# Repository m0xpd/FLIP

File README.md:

# FLIP

This repository describes a 'Bernoulli Gate', intended for switching applications in electronic music.

You can dive straight in to details of the [Eurorack module](https://github.com/m0xpd/Flip/blob/main/Eurorack/README.md), or a [stripboard layout for the circuit](https://github.com/m0xpd/FLIP/tree/main/Stripboard), or read more about the background and operation of this new design, below.

# Background

A Bernoulli Gate, named for Swiss mathematician and physicist [Daniel Bernoulli](https://en.wikipedia.org/wiki/Daniel_Bernoulli), takes a clock or gate input and routes it to one of two outputs, A & B, based on the 
value of an internally generated [Bernoulli Variable](https://web.stanford.edu/class/archive/cs/cs109/cs109.1178/lectureHandouts/070-bernoulli-binomial.pdf). When this (discrete, Boolean) random variable has value 1 the clock is routed to output A, and when the variable has value 0 the clock is routed to output B. The probability of the Bernoulli variable assuming value "1", p, is set by a front panel control (and/or by CV input). The probability of the variable assuming value "0" is (of course) 1-p. 

When the probability is set to p = 0.5, the process is equivalent to a "coin toss"; the input is routed to output A or B based on the outcome of a fair coin toss at each input onset. As p moves from the 0.5 value, the coin becomes increasingly "biased", with the outcome favouring one or other output. Larger values of p favors output A.

Bernoulli Gates have become familiar objects in modular synthesizers, the definitive example being Mutable Instruments' [Branches](https://pichenettes.github.io/mutable-instruments-documentation/modules/branches/) and various clones from other manufacturers. There is also a Bernoulli Gate within Mutable Instruments' [Marbles](https://pichenettes.github.io/mutable-instruments-documentation/modules/marbles/) module (and its clones), which is where it caught my interest. These implementations are achieved in software, running on microcontrollers.

# FLIP - a Hardware Bernoulli Gate

The Bernoulli Gate described in this repository is distinguished by being a completely **hardware realisation**. It generates the Bernoulli variable by a test of the instantaneous value of a linear ramp waveform. This ramp is running at a frequency several orders of magnitude above the clock frequencies typically used in synthesiser timing applications and is asynchronous to such input clocks/gates. Further, the ramp waveform is frequency-modulated by a second asynchronous signal, such that there is no possibility of 'phase' lock between an input clock and a subharmonic of the ramp waveform; the process is sufficiently random.

I should make it clear - I have absolutely nothing against the use of microcontrollers and DSP in modular synths, as I believe my work demonstrates. I designed FLIP for pleasure as a deliberate 'break' from playing with software-based systems in the recent development of my [STRACHEY](https://github.com/m0xpd/STRACHEY) sequencer. I based FLIP in hardware (rather than software) because I wanted the pleasure of something different. 

However, I should also confess to a feeling that we have become too ready to turn to soft solutions. There is something wasteful about having a little microcontroller (like Branches' ATMega88) sitting there doing something as simple as implementing (in that case two) Bernoulli Gates, even though it was *definitively the correct solution* for Mutable's commercial product. But I'm not designing for production - I'm enjoying myself, playing with ideas and materials I find to hand (often literally from the junk box). So - whilst I could easily have implemented my new Bernoulli Gate on an Atmel device or a PIC or similar, I think there remains something interesting and worthwhile in doing it 'old school'. 

I also recognise there are some members of the synth DIY community who actively do not like embedded/DSP. I repeat: **I'm NOT one of them**. But I'm pleased this project will be accessible to them.

Two versions of the hardware for FLIP are described in this repository. First, there is an implementation as a [Eurorack Module](https://github.com/m0xpd/Flip/blob/main/Eurorack/README.md), with full design details of the PCBs and front panel required for the 6HP module seen in the image at the head of this page. Second, I have included a [stripboard layout](https://github.com/m0xpd/Flip/blob/main/Stripboard/README.md) for the circuit for people who wish to build for a different format or who prefer to avoid the expense, delay, and minimum order quantities involved in making PCBs. The schematic for FLIP is presented as a single, system-level circuit in the [stripboard version](https://github.com/m0xpd/Flip/blob/main/Stripboard/README.md), whereas the [Eurorack version](https://github.com/m0xpd/Flip/blob/main/Eurorack/README.md) splits the system into two elements for implementation on two PCBs. Accordingly, those wishing to understand system operation might prefer to look at the schematic in the [stripboard folder](https://github.com/m0xpd/FLIP/tree/main/Stripboard) first. 

FLIP has two controls: the main 'probability' control and a control for the CV attenuverter. Advancing the probability control clockwise increases the probability that output A will be activated. When a positive CV is input, advancing the attenuverter control clockwise also increases the probability that A will 'fire' (the opposite sense applies when a negative CV is input). 

# Demo Video

A [short video](https://youtu.be/AdmhHrzYtKI), introduces FLIP and demonstrates its functions. The video is never going to win any oscars, not least as the camera is out of focus for the central 'demo' section. I don't know what changed between recording the music for the intro and 'closing credits' and the main, central demo portion. However, the message is clear, even if the image is not.    

# License

Material in this repository, including the circuit design and Eurorack implementation of FLIP, is published under a Creative Commons CC BY-SA 4.0 [License](https://github.com/m0xpd/Flip/blob/main/LICENSE.txt)

# Circuit Operation

Operation of the 'FLIP' Bernoulli Gate will now be described in some detail. Reference should be made to [this system-level schematic](https://github.com/m0xpd/Flip/blob/main/Stripboard/Graphics/m0xpd%20FLIP%20Bernoulli%20Gate.jpg) to which the component idents, circuit block names, and node names in the description below refer. [Note that these component idents differ from those used in the Eurorack version.]

FLIP derives a new value of a Bernoulli variable, p (as has been briefly introduced above) at the start of every clock input. This is done by comparing the instantaneous amplitude of a sawtooth wave to a threshold value. 

The sawtooth wave is generated by a 40106 oscillator (the block 'RAMP GENERATOR'), which is tuned (by adjustment of trimmer RV1, which should be set so there is approximately 1V on its wiper) to run at approximately 3.5kHz. The resulting sawtooth runs between voltages defined by the Schmitt trigger points of the 40106's inputs but the sawtooth is shifted to 0V mean by the high pass filter network C1,R3. Comparing this 'Saw' voltage with the fixed threshold voltage, 'Thres' (the magnitude of which is set either by the front panel probability potentiometer RV3 and/or by CV input to J2) produces a new Bernoulli variable, P at the output of the 'THRESHOLD COMPARATOR'. If the threshold is close to the bottom of the sawtooth's voltage range, the probability is close to (logical) one. If the threshold is close to the top of the sawtooth's voltage range, the probability is close to (logical) zero. the threshold voltage has been designed so it can be set slightly above or below the sawtooth's range, locking the probability to 1 or 0 (*and thereby setting the 'A' output on or off, with no switching action*), if required.

The photo below shows the 'Saw' waveform (in Yellow), the threshold voltage, 'Thres', set to just above the bottom of the sawtooth's voltage range (in Magenta) and the resulting Bernoulli variable, 'P' (in Cyan). The FM modulation of the saw oscillator (see below) has been disabled to make the image clearer and the results were captured from the prototype [stripboard](https://github.com/m0xpd/Flip/blob/main/Stripboard/README.md) system.

It is seen that the Bernoulli variable is almost always "1", as expected.

In the practical circuit, frequency response and slew rate limitations in the op-amp used as the comparator constrain behaviour when the threshold is placed closer to the top of the sawtooth's range.

The photo below shows behaviour when the threshold, 'Thres' is at about 50% of the positive range of the sawtooth.

It is seen that the Bernoulli variable is almost always "0"; this is the highest we can take the threshold voltage before it locks the gate "off". Taking the threshold value any higher in the practical circuit causes the comparator to fail to produce any 'non-zero' (in a logical sense) output. This is why the sawtooth wave - and the operation of FLIP - has been limited to 3.5kHz. 

The potential divider at the CV input, J2 (R13,R14) is loaded by the input resistance of the susbsequent attenuverter stage; this "loaded attenuator" produces around 6dB of attenuation in any configuration of the attenuverter. This allows a 5V CV signal to control the system, switching the gate from fully "on" to fully "off", whilst a higher CV input can achieve the same control at a lower attenuverter setting. Obviously, more subtle changes in configuration can be achieved with smaller control voltages, or with lower attenuverter settings.  

The external clock or gate signal is applied via J4 to FLIP's Schmitt trigger input circuit 'CLOCK IN' (with upward switchig threshold of 1.4V and downward threshold of 1.05V) to produce the gate signal, 'Input', which indicates an active input. The start of this input is detected by a typical passive differentiator / diode combination (C10,R30,D8), producing the signal 'dInput'.

The system is built around a trivial state machine which has two states, held on a SR flip-flop. I imlemented the flip-flop on 4001 (NOR) and 4081 (AND) gates, which were to hand (FLIP was designed around 'available materials') and provided sufficient logic resources for the remainder of the system. The transitions for the state machine were sufficient to define the Set and Reset signals:

The flip-flop is 'Set' when there is a leading edge of the clock AND the Bernoulli variable is 1 (Set = P.dInput).

The flip-flop is 'Reset' when 'Input' is false (Reset = _Input).

This system was found to work perfectly well in practical musical application, but offended me, as I understood there was possibility for a 'lock' between  a harmonic of the clock and the sawtooth wave, making the process less than random. I had anticipated this in design and arranged for the sawtooth oscillator to be voltage controlled. A second stage of the 40106 ('FM Osc') is used to implement an oscillator from which a triangular wave (at around 800Hz) is generated. This triangular voltage is used to frequency modulate the sawtooth, effectively removing the possibility of any 'lock' between the sawtooth and a periodic input signal. 

The photo below shows triggering with FM enabled:

In this case, the threshold has been set to approximately 0V and the Bernoulli variable is returning a true value approximately 35% of the time (but not achieving the 50% score of a "fair" system, as the 0V threshold is above the middle of the range determined by the two limiting cases shown in the previous two oscilloscope screen shots). Variation in the period of the sawtooth (and the resulting outputs from the comparator) caused by the frequency modulation is clearly visible.

FLIP's three outputs use a simple 'emitter follower' buffer scheme taught by Ken Stone. The 'A' output follows directly the 'Q' output of the flip-flop. The 'B' output must be derived from additional logic to AND the complemented flip-flop state _Q with the input clock/gate signal. Finally, an output is provided which mirrors the input. This output is driven by a further inversion of _Input, rather than by adding load to the output of the CLOCK IN circuit, which could impact the edge detection circuit.

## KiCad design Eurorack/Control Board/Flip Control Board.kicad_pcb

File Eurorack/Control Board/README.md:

# FLIP Control Board

This folder contains details of the Control Board for the Eurorack implementation of the FLIP Bernoulli Gate.

There is a KiCad [Project file](https://github.com/m0xpd/FLIP/blob/main/Eurorack/Control%20Board/Files/Flip%20Control%20Board.kicad_pro) a [schematic file](https://github.com/m0xpd/FLIP/blob/main/Eurorack/Control%20Board/Files/Flip%20Control%20Board.kicad_sch) and a [PCB file](https://github.com/m0xpd/FLIP/blob/main/Eurorack/Control%20Board/Files/Flip%20Control%20Board.kicad_pcb). 

[JLC](https://jlcpcb.com/) made my prototype PCBs (seen above) and did their usual great job.

There is also a schematic (click on the image below to open a larger version) and a BoM, saved as an [Excel file](https://github.com/m0xpd/FLIP/blob/main/Eurorack/Control%20Board/Files/Flip%20Control%20Board%20BoM.xlsx)

The BoM specifies the PJ398SM ('Thonkiconn') Jacks, Alpha 9mm potentiometer and Song Huei trimmer, which are important for mechanical as well as electrical compatability.

As I've mentioned on the [Main Board page](https://github.com/m0xpd/FLIP/blob/main/Eurorack/Main%20Board/README.md), this is only the second project I've developed in KiCad and I'm still feeling my way around. The only aspect of the control board PCB which I regret is the (default, library) footprint for the transistors Q1:3, which has unnecessarily small and close pads. It works, but it asks a lot during soldering. I will modify this if a "v2" revision is ever made.

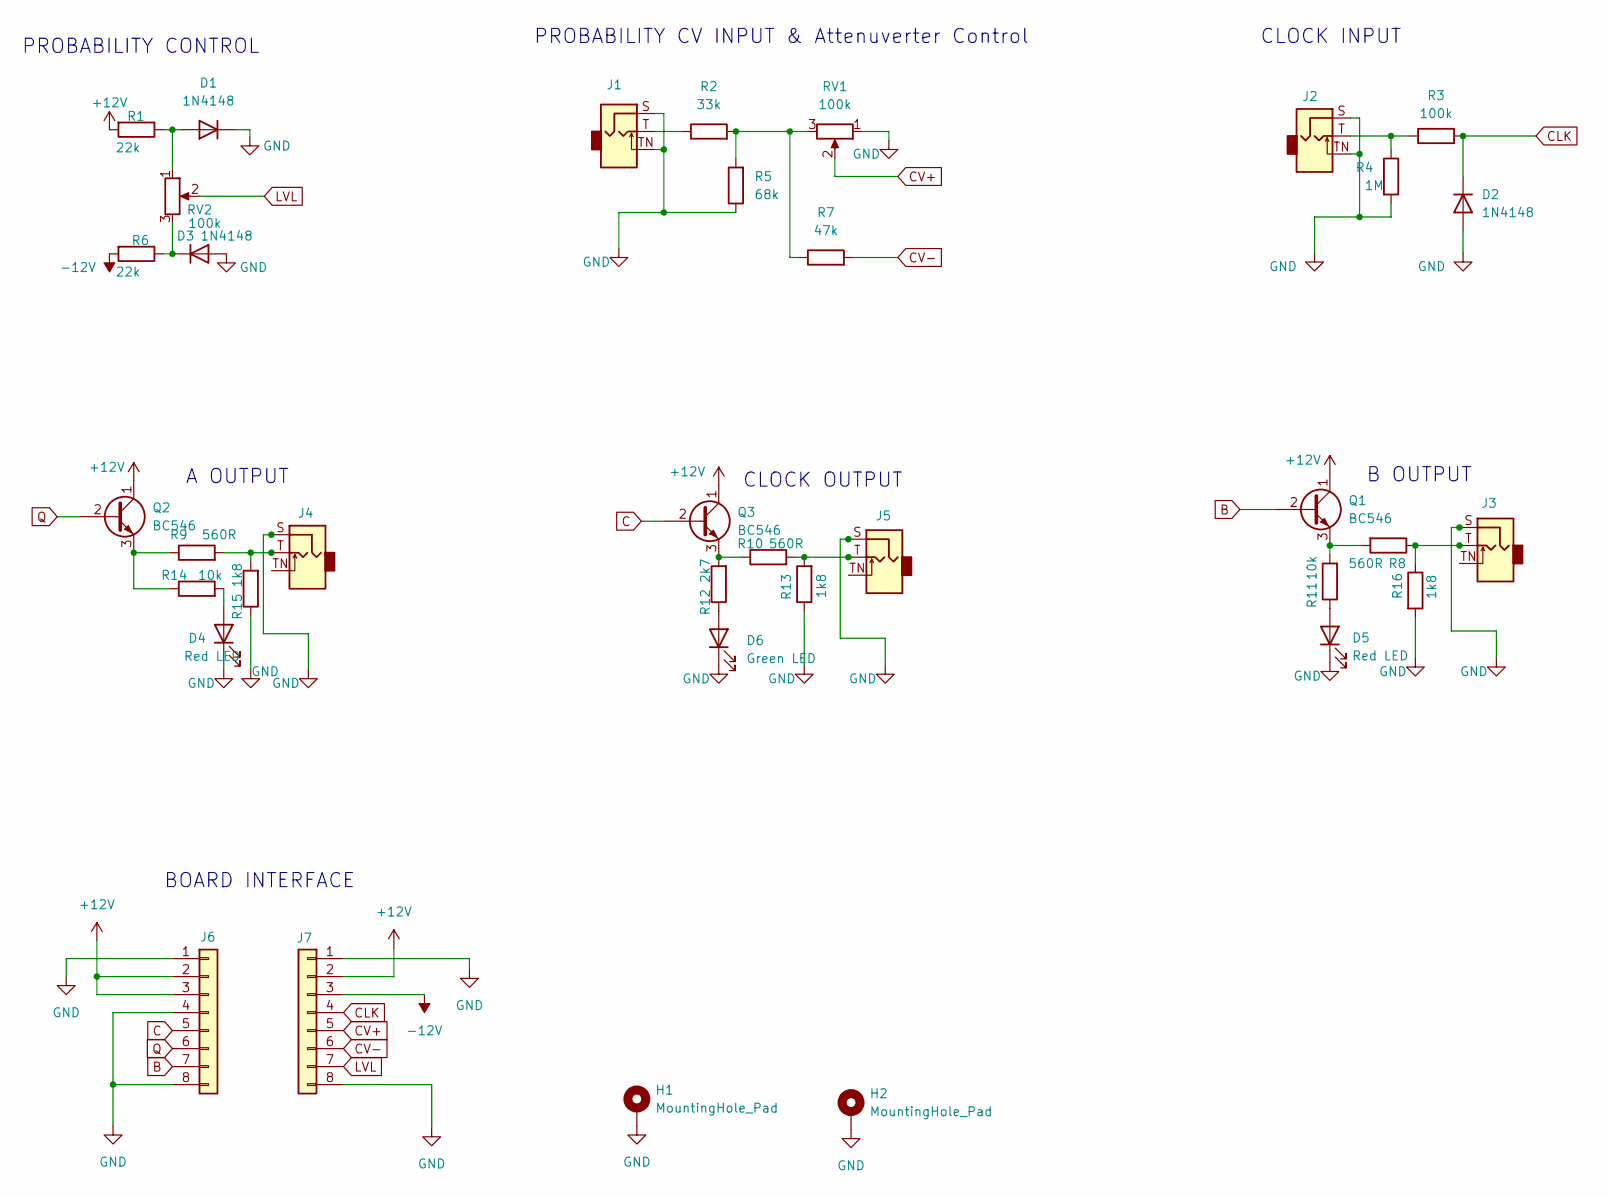
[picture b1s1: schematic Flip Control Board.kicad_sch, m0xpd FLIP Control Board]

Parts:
D1, D2, D3: 1N4148; D_DO-35_SOD27_P7.62mm_Horizontal
D4, D5: Red LED; LED_D3.0mm
D6: Green LED; LED_D3.0mm
H1, H2: MountingHole_Pad; MountingHole_3.2mm_M3_DIN965_Pad_TopBottom
J1, J2, J3, J4, J5: AudioJack2_SwitchT; Jack_3.5mm_QingPu_WQP-PJ398SM_Vertical_CircularHoles
J6, J7: Conn_01x08; PinHeader_1x08_P2.54mm_Vertical
Q1, Q2, Q3: BC546; TO-92_Inline
R1, R6: 22k; R_Axial_DIN0207_L6.3mm_D2.5mm_P7.62mm_Horizontal
R2: 33k; R_Axial_DIN0207_L6.3mm_D2.5mm_P7.62mm_Horizontal
R3: 100k; R_Axial_DIN0207_L6.3mm_D2.5mm_P7.62mm_Horizontal
R4: 1M; R_Axial_DIN0207_L6.3mm_D2.5mm_P7.62mm_Horizontal
R5: 68k; R_Axial_DIN0207_L6.3mm_D2.5mm_P7.62mm_Horizontal
R7: 47k; R_Axial_DIN0207_L6.3mm_D2.5mm_P7.62mm_Horizontal
R8, R9, R10: 560R; R_Axial_DIN0207_L6.3mm_D2.5mm_P7.62mm_Horizontal
R11, R14: 10k; R_Axial_DIN0207_L6.3mm_D2.5mm_P7.62mm_Horizontal
R12: 2k7; R_Axial_DIN0207_L6.3mm_D2.5mm_P7.62mm_Horizontal
R13, R15, R16: 1k8; R_Axial_DIN0207_L6.3mm_D2.5mm_P7.62mm_Horizontal
RV1, RV2: 100k; Potentiometer_Alpha_RD901F-40-00D_Single_Vertical_CircularH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

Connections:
+12V: J6.2, J6.3, J7.2, Q1.1 (C), Q2.1 (C), Q3.1 (C), R1.2
-12V: J7.3, R6.2
B: J6.7, Q1.2 (B)
C: J6.5, Q3.2 (B)
CLK: D2.1 (K), J7.4, R3.2
CV+: J7.5, RV1.2
CV-: J7.6, R7.2
GND: D1.1 (K), D2.2 (A), D3.2 (A), D4.1 (K), D5.1 (K), D6.1 (K), H1.1, H2.1, J1.S, J1.TN, J2.S, J2.TN, J3.S, J4.S, J5.S, J6.1, J6.4, J6.8, J7.1, J7.8, R4.2, R5.1, R13.1, R15.1, R16.2, RV1.1
LVL: J7.7, RV2.2
unnamed: D1.2 (A), R1.1, RV2.1
unnamed: D3.1 (K), R6.1, RV2.3
unnamed: D4.2 (A), R14.2
unnamed: D5.2 (A), R11.1
unnamed: D6.2 (A), R12.1
unnamed: J1.T, R2.1
unnamed: J2.T, R3.1, R4.1
unnamed: J3.T, R8.1, R16.1
unnamed: J4.T, R9.2, R15.2
unnamed: J5.T, R10.2, R13.2
unnamed: Q1.3 (E), R8.2, R11.2
unnamed: Q2.3 (E), R9.1, R14.1
unnamed: Q3.3 (E), R10.1, R12.2
unnamed: R2.2, R5.2, R7.1, RV1.3
Q: J6.6, Q2.2 (B)

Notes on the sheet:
B OUTPUT
A OUTPUT
CLOCK OUTPUT
PROBABILITY CONTROL
BOARD INTERFACE
CLOCK INPUT
PROBABILITY CV INPUT & Attenuverter Control

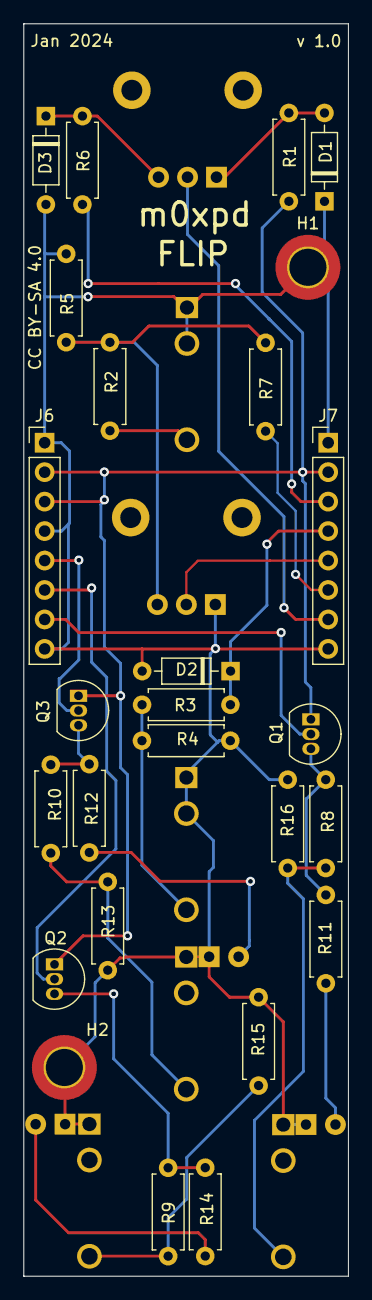
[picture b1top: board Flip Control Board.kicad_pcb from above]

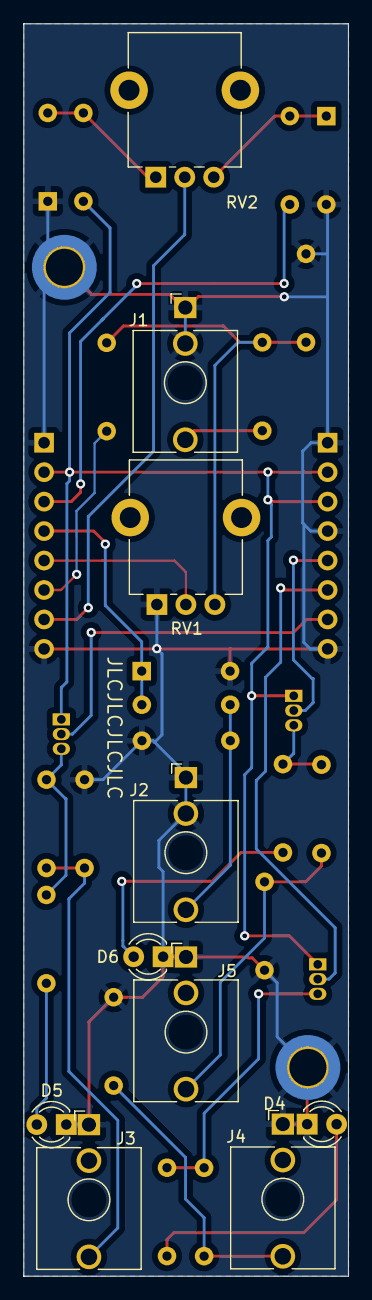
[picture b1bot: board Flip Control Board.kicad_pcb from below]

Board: 2 copper layers, 28.0 x 108.0 mm, 36 parts (10 on the bottom side), 24 nets.

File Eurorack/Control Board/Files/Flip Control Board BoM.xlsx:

Source: | /Users/pauldarlington/Documents/Analog Synth/Bernoulli Gate/Flip Control Board/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
Date: | Tuesday, January 09, 2024 at 09:57:17 AM
Tool: | Eeschema 7.0.9
Generator: | /Applications/KiCad/KiCad.app/Contents/SharedSupport/plugins/bom_csv_grouped_by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
Component Count: | 36
Collated Components:
Item | Qty | Reference(s) | Value | Notes | Link / Suppliers | LibPart | Footprint | Datasheet | DNP | Sim.Device | Sim.Pins
1 | 3 | D1, D2, D3 | 1N4148 |  |  | Diode:1N4148 | Diode_THT:D_DO-35_SOD27_P7.62mm_Horizontal | https://assets.nexperia.com/documents/data-sheet/1N4148_1N4448.pdf |  | D | 1=K 2=A
2 | 2 | D4, D5 | Red LED | 2mm "Tower/Lighthouse" type | https://store.brightcomponents.co.uk/product-category/leds/t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 | Device:LED | LED_THT:LED_D3.0mm | ~
3 | 1 | D6 | Green LED | 2mm "Tower/Lighthouse" type | https://www.switchelectronics.co.uk/products/green-2mm-light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 | Device:LED | LED_THT:LED_D3.0mm | ~
4 | 2 | H1, H2 | MountingHole_Pad | Fit M3 bolts, nuts, spacers & washers |  | Mechanical:MountingHole_Pad | MountingHole:MountingHole_3.2mm_M3_DIN965_Pad_TopBottom | ~
5 | 5 | J1, J2, J3, J4, J5 | AudioJack2_SwitchT | Thonkiconn PJ398SM | https://www.thonk.co.uk/shop/thonkiconn/ | Connector_Audio:AudioJack2_SwitchT | Connector_Audio:Jack_3.5mm_QingPu_WQP-PJ398SM_Vertical_CircularHoles | ~
6 | 2 | J6, J7 | Conn_01x08 | Female |  | Connector_Generic:Conn_01x08 | Connector_PinHeader_2.54mm:PinHeader_1x08_P2.54mm_Vertical | ~
7 | 3 | Q1, Q2, Q3 | BC546 | Substitute BC547 or (with appropriate rotation) 2n3904, etc |  | Transistor_BJT:BC546 | Package_TO_SOT_THT:TO-92_Inline | https://www.onsemi.com/pub/Collateral/BC550-D.pdf
8 | 2 | R1, R6 | 22k |  |  | Device:R | Resistor_THT:R_Axial_DIN0207_L6.3mm_D2.5mm_P7.62mm_Horizontal | ~
9 | 1 | R2 | 33k |  |  | Device:R | Resistor_THT:R_Axial_DIN0207_L6.3mm_D2.5mm_P7.62mm_Horizontal | ~
10 | 2 | R11, R14 | 10k * | * Select for Red LED
11 | 1 | R12 | 2k7 * | * Select for Green LED
12 | 1 | R3 | 100k |  |  | Device:R | Resistor_THT:R_Axial_DIN0207_L6.3mm_D2.5mm_P7.62mm_Horizontal | ~
13 | 1 | R4 | 1M |  |  | Device:R | Resistor_THT:R_Axial_DIN0207_L6.3mm_D2.5mm_P7.62mm_Horizontal | ~
14 | 1 | R5 | 68k |  |  | Device:R | Resistor_THT:R_Axial_DIN0207_L6.3mm_D2.5mm_P7.62mm_Horizontal | ~
15 | 1 | R7 | 47k |  |  | Device:R | Resistor_THT:R_Axial_DIN0207_L6.3mm_D2.5mm_P7.62mm_Horizontal | ~
16 | 3 | R8, R9, R10 | 560R |  |  | Device:R | Resistor_THT:R_Axial_DIN0207_L6.3mm_D2.5mm_P7.62mm_Horizontal | ~
17 | 3 | R13, R15, R16 | 1k8 |  |  | Device:R | Resistor_THT:R_Axial_DIN0207_L6.3mm_D2.5mm_P7.62mm_Horizontal | ~
18 | 1 | RV1 | 100k (Linear) | Song Huei 9mm Trimmer | https://www.thonk.co.uk/shop/ttpots/ | Device:R_Potentiometer | Potentiometer_THT:Potentiometer_Alpha_RD901F-40-00D_Single_Vertical_CircularHol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 | ~
19 | 1 | RV2 | 100k (Linear) | Alpha 9mm Pot | https://www.thonk.co.uk/shop/alpha-9mm-pots-vertical-t18/

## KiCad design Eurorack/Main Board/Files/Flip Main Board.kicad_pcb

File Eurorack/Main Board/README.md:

# FLIP Main Board

This [folder](https://github.com/m0xpd/FLIP/tree/main/Eurorack/Main%20Board) contains details of the Main Board for the Eurorack implementation of the FLIP Bernoulli Gate, expressed as a KiCad project.

There is a KiCad [Project file](https://github.com/m0xpd/FLIP/blob/main/Eurorack/Main%20Board/Files/Flip%20Main%20Board.kicad_pro) a [schematic file](https://github.com/m0xpd/FLIP/blob/main/Eurorack/Main%20Board/Files/Flip%20Main%20Board.kicad_sch) and a [PCB file](https://github.com/m0xpd/FLIP/blob/main/Eurorack/Main%20Board/Files/Flip%20Main%20Board.kicad_pcb). 

[JLC](https://jlcpcb.com/) made my prototype PCBs (seen above) and did their usual great job.

There is also a schematic (click on the image below to open a larger version) and a BoM, saved as an [Excel file](https://github.com/m0xpd/FLIP/blob/main/Eurorack/Main%20Board/Files/Flip%20Main%20Board%20BoM.xlsx)

The schematic above follows pretty closely the [system-level schematic presented in the stripboard folder](https://github.com/m0xpd/Flip/blob/main/Stripboard/Graphics/m0xpd%20FLIP%20Bernoulli%20Gate.jpg) apart from the fact that I have swapped the inverters (from the 40106) on the input to the Clock output stage and in the State Machine with unused gates in the 4001 package. This was done solely for convenience in laying out the PCB and has no impact on system operation - the Schmitt trigger inputs were not being exploited and the NOR gates can work perfectly well as inverters. Obviously, all the other 'missing' elements (user interface components, output buffers, etc) are on the [control board](https://github.com/m0xpd/FLIP/tree/main/Eurorack/Control%20Board).

This is only the second project I've developed in KiCad and I'm still feeling my way around. There are two issues on the main board PCB which could be better. The first is the (default, library) footprint for the transistors Q1:3, which has unnecessarily small and close pads. It works, but it asks a lot during the soldering phase! The second is proximity of the 12V line to mounting hole H2 on the bottom of the board; there isn't really enough safe clearance here for a full M3 washer. I managed this issue on my first build by using an insulated spacer between the main and control boards at this position; you could also use a single insulated washer. Whilst neither of these issues prevent use of the main board PCB as it stands, I will modify both if a "v2" revision of the main board PCB is ever made.

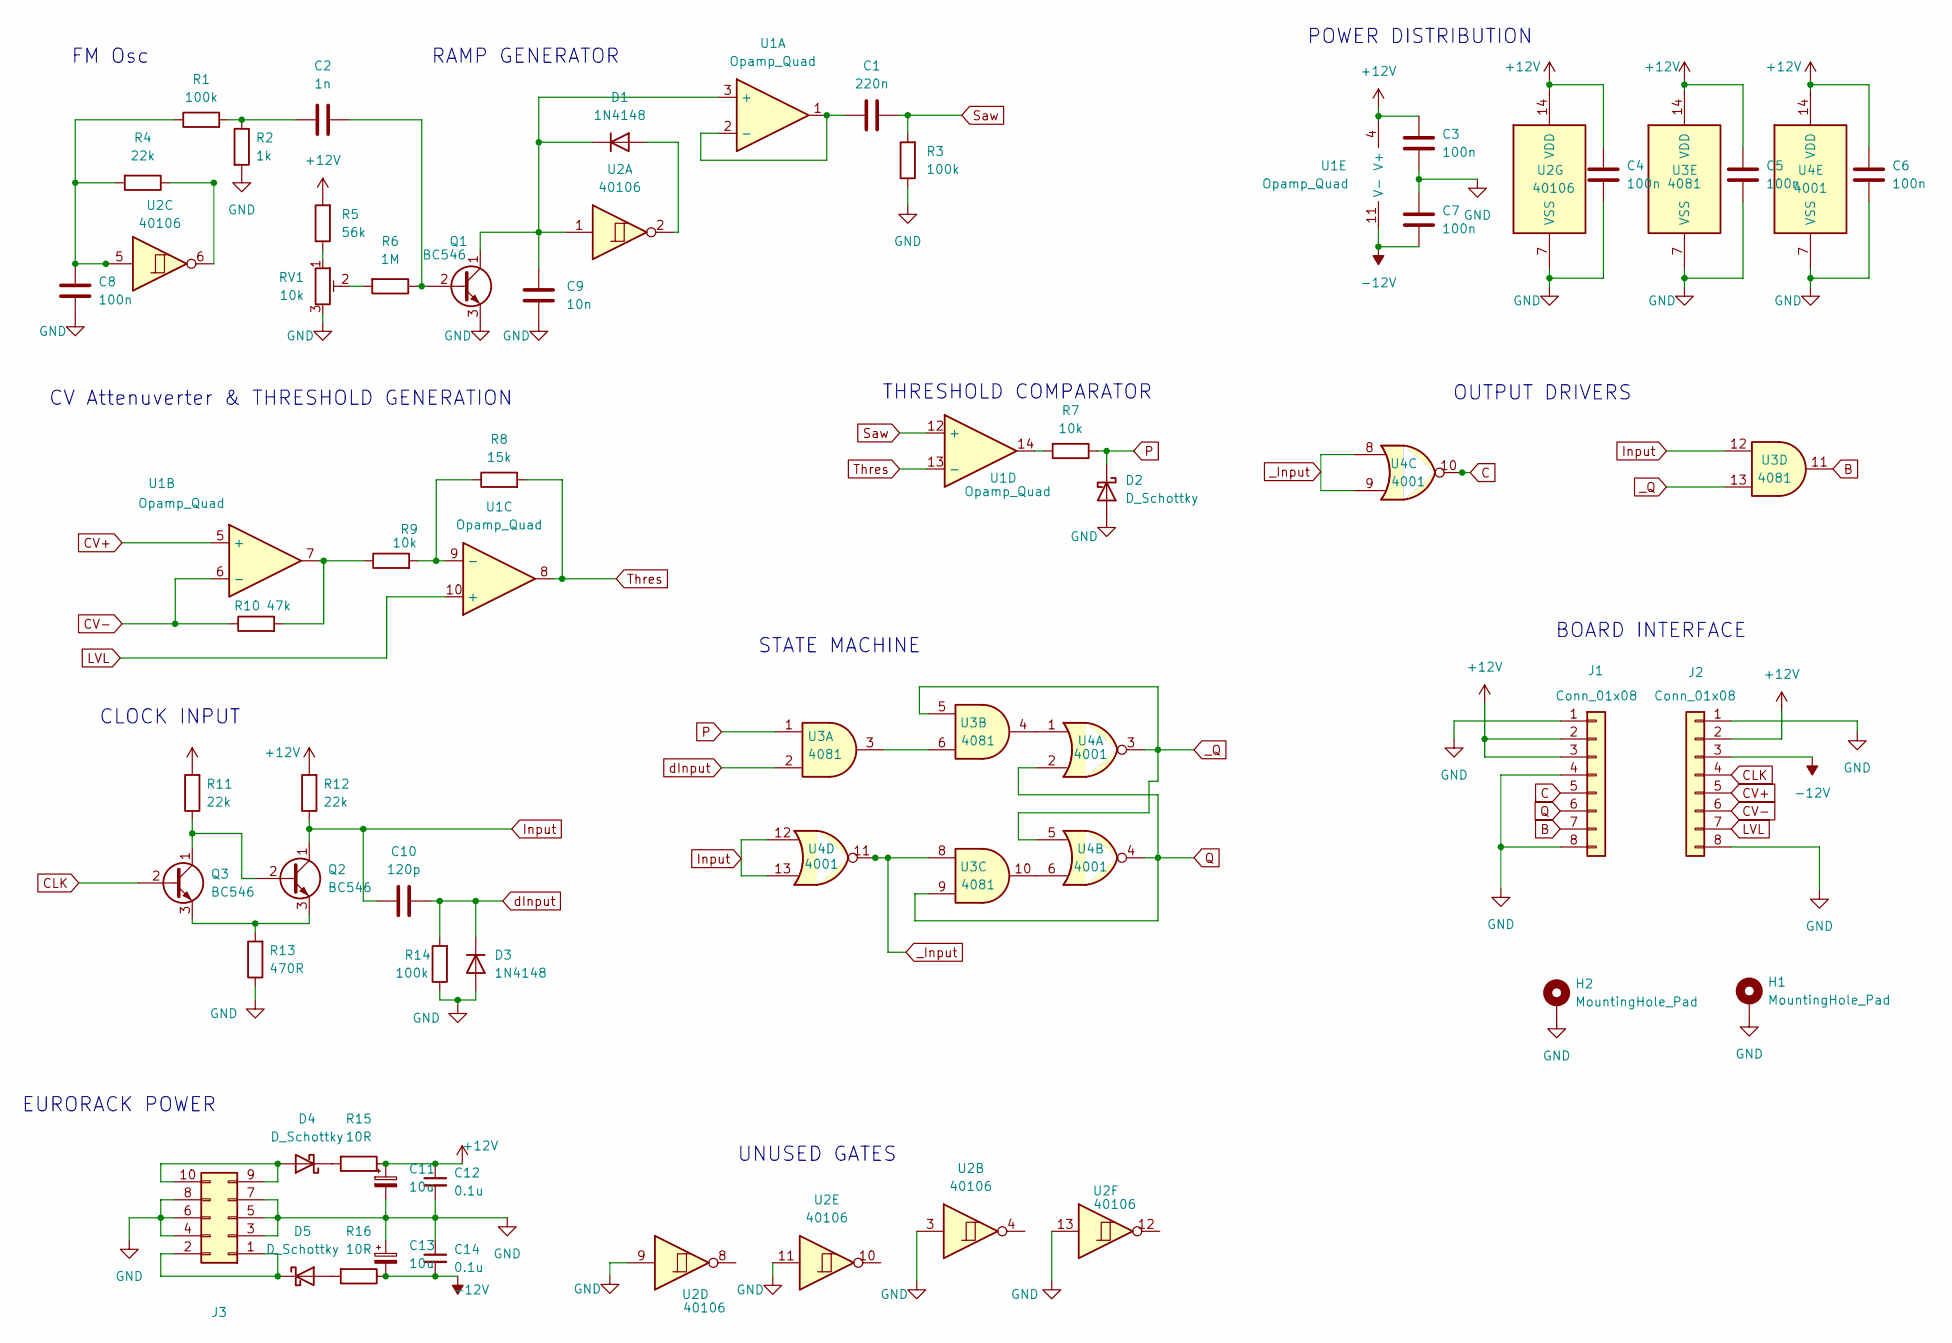
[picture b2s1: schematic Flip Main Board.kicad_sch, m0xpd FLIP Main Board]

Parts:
C1: 220n; C_Disc_D4.3mm_W1.9mm_P5.00mm
C2: 1n; C_Disc_D3.8mm_W2.6mm_P2.50mm
C3, C4, C5, C6, C7, C8: 100n; C_Disc_D4.3mm_W1.9mm_P5.00mm
C9: 10n; C_Disc_D4.3mm_W1.9mm_P5.00mm
C10: 120p; C_Disc_D3.8mm_W2.6mm_P2.50mm
C11, C13: 10u; CP_Radial_D6.3mm_P2.50mm
C12, C14: 0.1u; C_Disc_D4.3mm_W1.9mm_P5.00mm
D1: 1N4148; D_DO-35_SOD27_P2.54mm_Vertical_KathodeUp
D2: D_Schottky; D_DO-35_SOD27_P2.54mm_Vertical_AnodeUp
D3: 1N4148; D_DO-35_SOD27_P7.62mm_Horizontal
D4, D5: D_Schottky; D_DO-35_SOD27_P7.62mm_Horizontal
H1, H2: MountingHole_Pad; MountingHole_3.2mm_M3_DIN965_Pad_TopBottom
J1, J2: Conn_01x08; PinHeader_1x08_P2.54mm_Vertical
J3: Conn_02x05_Odd_Even; IDC-Header_2x05_P2.54mm_Vertical
Q1, Q2, Q3: BC546; TO-92_Inline
R1, R14: 100k; R_Axial_DIN0207_L6.3mm_D2.5mm_P7.62mm_Horizontal
R2: 1k; R_Axial_DIN0207_L6.3mm_D2.5mm_P7.62mm_Horizontal
R3: 100k; R_Axial_DIN0207_L6.3mm_D2.5mm_P2.54mm_Vertical
R4, R11, R12: 22k; R_Axial_DIN0207_L6.3mm_D2.5mm_P2.54mm_Vertical
R5: 56k; R_Axial_DIN0207_L6.3mm_D2.5mm_P7.62mm_Horizontal
R6: 1M; R_Axial_DIN0207_L6.3mm_D2.5mm_P7.62mm_Horizontal
R7: 10k; R_Axial_DIN0207_L6.3mm_D2.5mm_P2.54mm_Vertical
R8: 15k; R_Axial_DIN0207_L6.3mm_D2.5mm_P2.54mm_Vertical
R9: 10k; R_Axial_DIN0207_L6.3mm_D2.5mm_P7.62mm_Horizontal
R10: 47k; R_Axial_DIN0207_L6.3mm_D2.5mm_P2.54mm_Vertical
R13: 470R; R_Axial_DIN0207_L6.3mm_D2.5mm_P2.54mm_Vertical
R15, R16: 10R; R_Axial_DIN0207_L6.3mm_D2.5mm_P7.62mm_Horizontal
RV1: 10k; Potentiometer_Bourns_3296W_Vertical
U1: Opamp_Quad; DIP-14_W7.62mm_LongPads
U2: 40106; DIP-14_W7.62mm_LongPads
U3: 4081; DIP-14_W7.62mm_LongPads
U4: 4001; DIP-14_W7.62mm_LongPads

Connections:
+12V: C3.1, C4.1, C5.1, C6.1, C11.1, C12.1, J1.2, J1.3, J2.2, R5.2, R11.2, R12.2, R15.1, U1.4 (V+), U2.14 (VDD), U3.14 (VDD), U4.14 (VDD)
-12V: C7.2, C13.2, C14.2, J2.3, R16.1, U1.11 (V-)
B: J1.7, U3.11
C: J1.5, U4.10
CLK: J2.4, Q3.2 (B)
CV+: J2.5, U1.5 (+)
CV-: J2.6, R10.1, U1.6 (-)
GND: C3.2, C4.2, C5.2, C6.2, C7.1, C8.2, C9.2, C11.2, C12.2, C13.1, C14.1, D2.2 (A), D3.2 (A), H1.1, H2.1, J1.1, J1.4, J1.8, J2.1, J2.8, J3.3, J3.4, J3.5, J3.6, J3.7, J3.8, Q1.3 (E), R2.2, R3.1, R13.1, R14.1, RV1.3, U2.3, U2.7 (VSS), U2.9, U2.11, U2.13, U3.7 (VSS), U4.7 (VSS)
Input: C10.1, Q2.1 (C), R12.1, U3.12, U4.12, U4.13
LVL: J2.7, U1.10 (+)
unnamed: C2.1, R1.2, R2.1
unnamed: C8.1, R1.1, R4.2, U2.5
unnamed: D1.2 (A), U2.2
unnamed: C9.1, D1.1 (K), Q1.1 (C), U1.3 (+), U2.1
unnamed: D4.2 (A), J3.9, J3.10
unnamed: D4.1 (K), R15.2
unnamed: D5.2 (A), R16.2
unnamed: D5.1 (K), J3.1, J3.2
unnamed: C2.2, Q1.2 (B), R6.1
unnamed: Q2.2 (B), Q3.1 (C), R11.1
unnamed: Q2.3 (E), Q3.3 (E), R13.2
unnamed: R4.1, U2.6
unnamed: R5.1, RV1.1
unnamed: R6.2, RV1.2
unnamed: R7.2, U1.14
unnamed: R9.1, R10.2, U1.7
unnamed: C1.1, U1.1, U1.2 (-)
unnamed: R8.1, R9.2, U1.9 (-)
unnamed: U3.3, U3.6
unnamed: U3.4, U4.1
unnamed: U3.10, U4.6
P: D2.1 (K), R7.1, U3.1
Q: J1.6, U3.9, U4.2, U4.4
Saw: C1.2, R3.2, U1.12 (+)
Thres: R8.2, U1.8, U1.13 (-)
_Input: U3.8, U4.8, U4.9, U4.11
_Q: U3.5, U3.13, U4.3, U4.5
dInput: C10.2, D3.1 (K), R14.2, U3.2

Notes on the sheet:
CV Attenuverter & THRESHOLD GENERATION
EURORACK POWER
OUTPUT DRIVERS
STATE MACHINE
RAMP GENERATOR
BOARD INTERFACE
CLOCK INPUT
UNUSED GATES
THRESHOLD COMPARATOR
POWER DISTRIBUTION
FM Osc

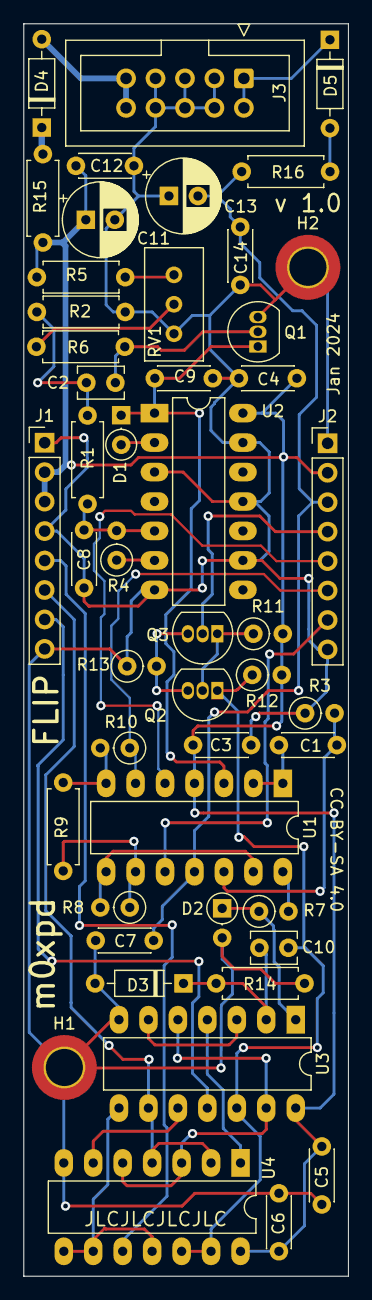
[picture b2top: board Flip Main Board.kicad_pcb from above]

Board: 2 copper layers, 28.0 x 108.0 mm, 48 parts (0 on the bottom side), 38 nets.

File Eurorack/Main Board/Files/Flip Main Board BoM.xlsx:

Source: | /Users/pauldarlington/Documents/Analog Synth/Bernoulli Gate/Flip Main Board/Fli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
Date: | Tuesday, January 09, 2024 at 03:11:41 PM
Tool: | Eeschema 7.0.9
Generator: | /Applications/KiCad/KiCad.app/Contents/SharedSupport/plugins/bom_csv_grouped_by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
Component Count: | 48
Collated Components:
Item | Qty | Reference(s) | Value | Notes |  | LibPart | Footprint | Datasheet | DNP | Sim.Device | Sim.Pins
1 | 1 | C1 | 220n | All capacitors ceramic… |  | Device:C | Capacitor_THT:C_Disc_D4.3mm_W1.9mm_P5.00mm | ~
2 | 1 | C2 | 1n |  |  | Device:C | Capacitor_THT:C_Disc_D3.8mm_W2.6mm_P2.50mm | ~
3 | 6 | C3, C4, C5, C6, C7, C8 | 100n |  |  | Device:C | Capacitor_THT:C_Disc_D4.3mm_W1.9mm_P5.00mm | ~
4 | 1 | C9 | 10n |  |  | Device:C | Capacitor_THT:C_Disc_D4.3mm_W1.9mm_P5.00mm | ~
5 | 1 | C10 | 120p |  |  | Device:C | Capacitor_THT:C_Disc_D3.8mm_W2.6mm_P2.50mm | ~
6 | 2 | C11, C13 | 10u | except C11, C13: radial electrolytic |  | Device:C_Polarized_Small | Capacitor_THT:CP_Radial_D6.3mm_P2.50mm | ~
7 | 2 | C12, C14 | 0.1u |  |  | Device:C_Small | Capacitor_THT:C_Disc_D4.3mm_W1.9mm_P5.00mm | ~
8 | 1 | D1 | 1N4148 |  |  | Diode:1N4148 | Diode_THT:D_DO-35_SOD27_P2.54mm_Vertical_KathodeUp | https://assets.nexperia.com/documents/data-sheet/1N4148_1N4448.pdf |  | D | 1=K 2=A
9 | 1 | D2 | BAT42 |  |  | Device:D_Schottky | Diode_THT:D_DO-35_SOD27_P2.54mm_Vertical_AnodeUp | ~
10 | 1 | D3 | 1N4148 |  |  | Diode:1N4148 | Diode_THT:D_DO-35_SOD27_P7.62mm_Horizontal | https://assets.nexperia.com/documents/data-sheet/1N4148_1N4448.pdf |  | D | 1=K 2=A
11 | 2 | D4, D5 | 1N5157 |  |  | Device:D_Schottky | Diode_THT:D_DO-35_SOD27_P7.62mm_Horizontal | ~
12 | 2 | H1, H2 | MountingHole_Pad | M3 |  | Mechanical:MountingHole_Pad | MountingHole:MountingHole_3.2mm_M3_DIN965_Pad_TopBottom | ~
13 | 2 | J1, J2 | Conn_01x08 |  |  | Connector_Generic:Conn_01x08 | Connector_PinHeader_2.54mm:PinHeader_1x08_P2.54mm_Vertical | ~
14 | 1 | J3 | Conn_02x05_Odd_Even | Eurorack Power; Shrouded 2*5 2.54mm Plug |  | Connector_Generic:Conn_02x05_Odd_Even | Connector_IDC:IDC-Header_2x05_P2.54mm_Vertical | ~
15 | 3 | Q1, Q2, Q3 | BC546 | Substitute: BC547 etc or (with rotation) 2n3904 etc |  | Transistor_BJT:BC546 | Package_TO_SOT_THT:TO-92_Inline | https://www.onsemi.com/pub/Collateral/BC550-D.pdf
16 | 2 | R1, R14 | 100k |  |  | Device:R | Resistor_THT:R_Axial_DIN0207_L6.3mm_D2.5mm_P7.62mm_Horizontal | ~
17 | 1 | R2 | 1k |  |  | Device:R | Resistor_THT:R_Axial_DIN0207_L6.3mm_D2.5mm_P7.62mm_Horizontal | ~
18 | 1 | R3 | 100k |  |  | Device:R | Resistor_THT:R_Axial_DIN0207_L6.3mm_D2.5mm_P2.54mm_Vertical | ~
19 | 3 | R4, R11, R12 | 22k |  |  | Device:R | Resistor_THT:R_Axial_DIN0207_L6.3mm_D2.5mm_P2.54mm_Vertical | ~
20 | 1 | R5 | 56k |  |  | Device:R | Resistor_THT:R_Axial_DIN0207_L6.3mm_D2.5mm_P7.62mm_Horizontal | ~
21 | 1 | R6 | 1M |  |  | Device:R | Resistor_THT:R_Axial_DIN0207_L6.3mm_D2.5mm_P7.62mm_Horizontal | ~
22 | 1 | R7 | 10k |  |  | Device:R | Resistor_THT:R_Axial_DIN0207_L6.3mm_D2.5mm_P2.54mm_Vertical | ~
23 | 1 | R8 | 15k |  |  | Device:R | Resistor_THT:R_Axial_DIN0207_L6.3mm_D2.5mm_P2.54mm_Vertical | ~
24 | 1 | R9 | 10k |  |  | Device:R | Resistor_THT:R_Axial_DIN0207_L6.3mm_D2.5mm_P7.62mm_Horizontal | ~
25 | 1 | R10 | 47k |  |  | Device:R | Resistor_THT:R_Axial_DIN0207_L6.3mm_D2.5mm_P2.54mm_Vertical | ~
26 | 1 | R13 | 470R |  |  | Device:R | Resistor_THT:R_Axial_DIN0207_L6.3mm_D2.5mm_P2.54mm_Vertical | ~
27 | 2 | R15, R16 | 10R |  |  | Device:R | Resistor_THT:R_Axial_DIN0207_L6.3mm_D2.5mm_P7.62mm_Horizontal | ~
28 | 1 | RV1 | 10k | Multi-turn trimmer |  | Device:R_Potentiometer_Trim | Potentiometer_THT:Potentiometer_Bourns_3296W_Vertical | ~
29 | 1 | U1 | TL084 | Optional Substitute: TL074 |  | Device:Opamp_Quad | Package_DIP:DIP-14_W7.62mm_LongPads | ~
30 | 1 | U2 | 40106 |  |  | 4xxx:40106 | Package_DIP:DIP-14_W7.62mm_LongPads | https://assets.nexperia.com/documents/data-sheet/HEF40106B.pdf
31 | 1 | U3 | 4081 |  |  | 4xxx:4081 | Package_DIP:DIP-14_W7.62mm_LongPads | http://www.intersil.com/content/dam/Intersil/documents/cd40/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
32 | 1 | U4 | 4001 |  |  | 4xxx:4001 | Package_DIP:DIP-14_W7.62mm_LongPads | http://www.intersil.com/content/dam/Intersil/documents/cd40/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

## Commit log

2024-01-04 Rename Stripboard/Vero Prototype.jpg to Stripboard/Graphics/Vero Prototype.jpg
2024-01-07 Rename Triggering at Bottom of Range.jpg to Graphics/Triggering at Bottom of Range.jpg
2024-01-07 Rename Triggering at Top of Range.jpg to Graphics/Triggering at Top of Range.jpg
2024-01-09 Rename Eurorack/Main Board/Flip Main Board.jpg to Eurorack/Main Board/Files/Flip Main Board.jpg
2024-01-09 Rename Eurorack/Main Board/Flip Main Board.kicad_pcb to Eurorack/Main Board/Files/Flip Main Board.kicad_pcb
2024-01-09 Rename Eurorack/Main Board/Flip Main Board.kicad_pro to Eurorack/Main Board/Files/Flip Main Board.kicad_pro
2024-01-09 Rename Eurorack/Main Board/Flip Main Board.kicad_sch to Eurorack/Main Board/Files/Flip Main Board.kicad_sch
2024-01-09 Rename Eurorack/Control Board/Flip Control Board BoM.xlsx to Eurorack/Control Board/Files/Flip Control Board BoM.xlsx
2024-01-09 Rename Eurorack/Control Board/Flip Control Board.jpg to Eurorack/Control Board/Files/Flip Control Board.jpg
2024-01-09 Rename Eurorack/Control Board/Flip Control Board.kicad_pcb to Eurorack/Control Board/Files/Flip Control Board.kicad_pcb
2024-01-09 Rename Eurorack/Control Board/Flip Control Board.kicad_pro to Eurorack/Control Board/Files/Flip Control Board.kicad_pro
2024-01-09 Rename Eurorack/Control Board/Flip Control Board.kicad_sch to Eurorack/Control Board/Files/Flip Control Board.kicad_sch
2024-01-09 Rename Eurorack/Front Panel/Flip Front Panel.kicad_pcb to Eurorack/Front Panel/Files/Flip Front Panel.kicad_pcb
2024-01-09 Rename Eurorack/Front Panel/Flip Front Panel.kicad_pro to Eurorack/Front Panel/Files/Flip Front Panel.kicad_pro
2024-01-09 Rename Eurorack/Front Panel/Flip Front Panel.kicad_sch to Eurorack/Front Panel/Files/Flip Front Panel.kicad_sch
2024-01-09 Rename Eurorack/Main Board/Flip Main Board BoM.xlsx to Eurorack/Main Board/Files/Flip Main Board BoM.xlsx

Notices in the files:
Eurorack/Control Board/Flip Control Board.kicad_sch:
Published under CC BY-SA 4.0 License
Eurorack/Main Board/Files/Flip Main Board.kicad_sch:
Published under CC BY-SA License
